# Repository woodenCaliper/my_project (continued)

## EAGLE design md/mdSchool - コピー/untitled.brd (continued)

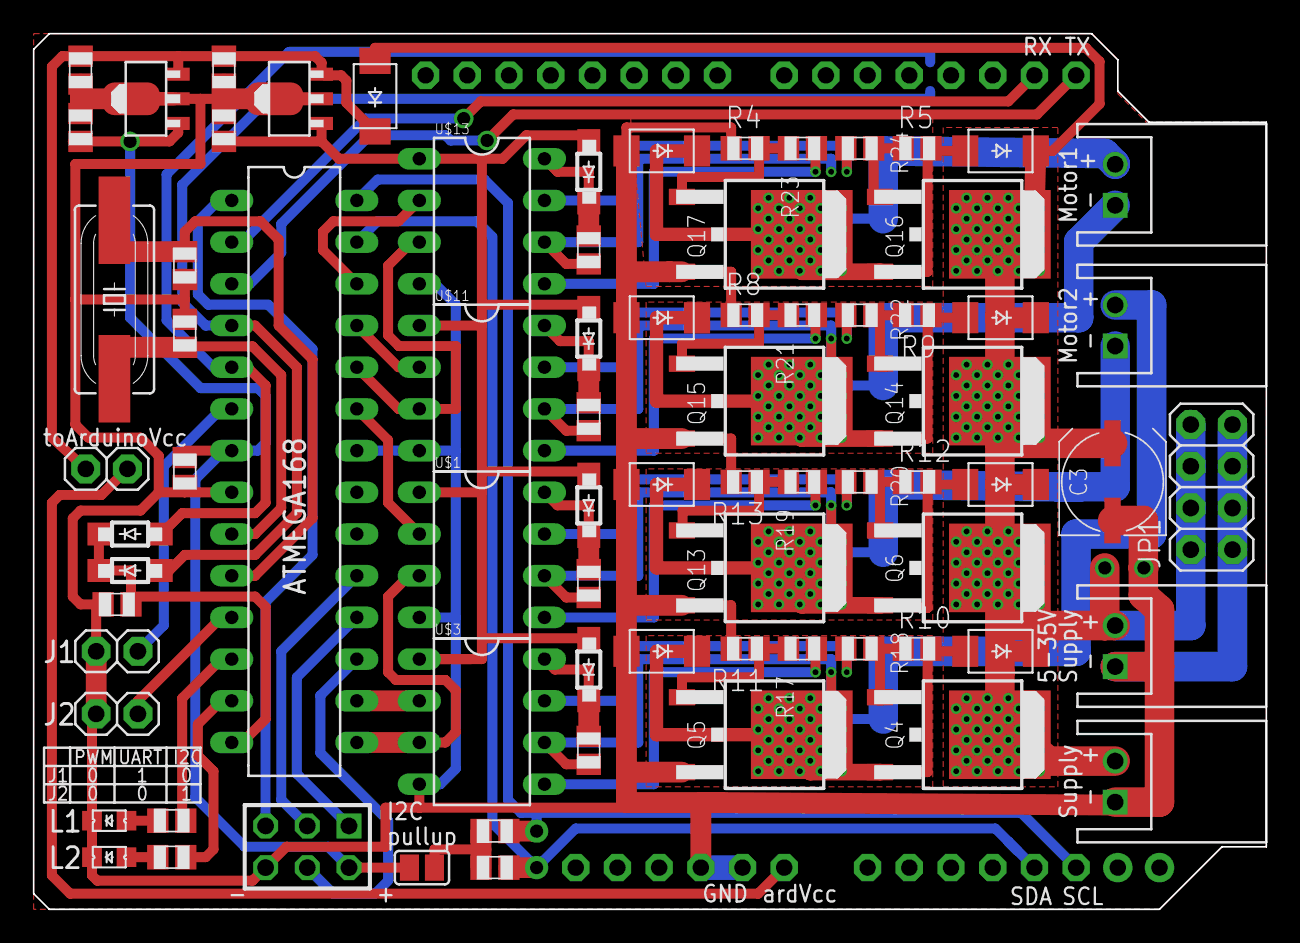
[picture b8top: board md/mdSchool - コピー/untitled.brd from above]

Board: 2 copper layers, 75.1 x 53.3 mm, 77 parts (0 on the bottom side), 56 nets.
